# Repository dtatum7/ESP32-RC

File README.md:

ESP32 based remote control system with 8 PWM outputs reconfigurable as controller ADC inputs with SparkFun QWIIC / Adafruit STEMMA connections for easy customization.

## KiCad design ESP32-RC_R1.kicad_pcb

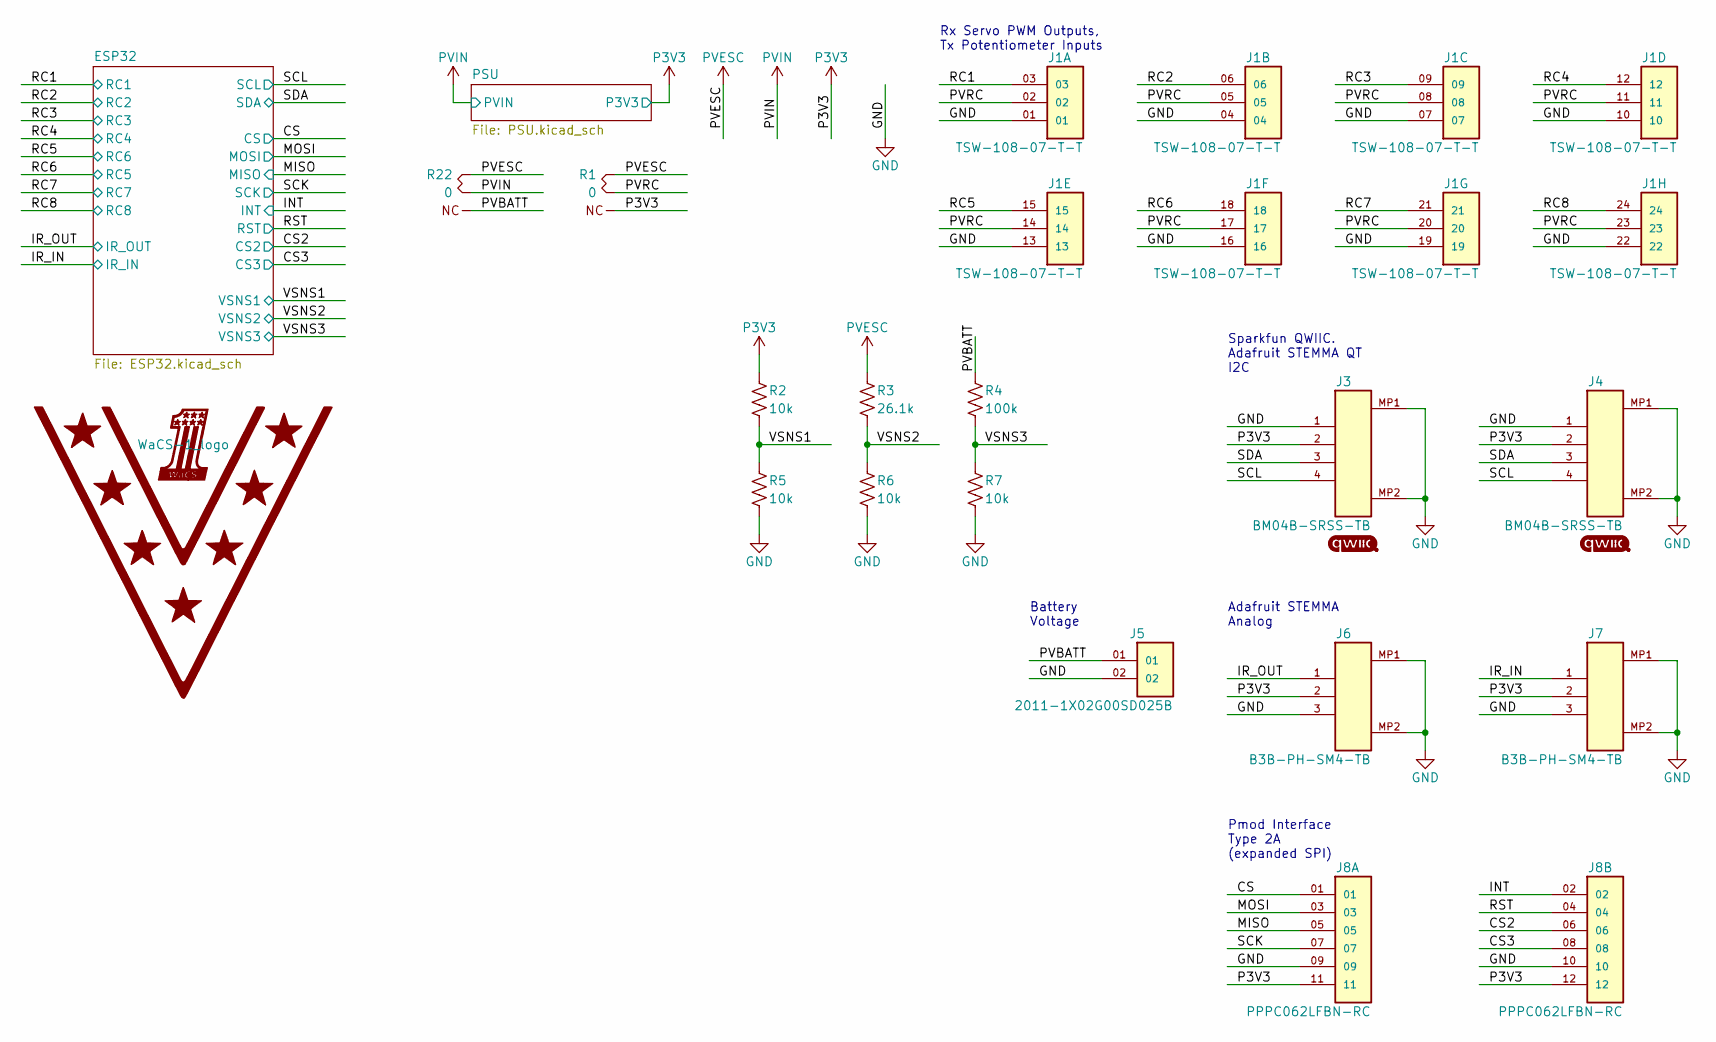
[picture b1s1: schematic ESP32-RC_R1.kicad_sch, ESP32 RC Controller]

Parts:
G1, G2: QWIIC_logo; MPN QWIIC_logo
G5: WaCS-1_logo; MPN WaCS-1_logo
G6: Champion logo; MPN Champion_Logo
J1: TSW-108-07-T-T; SAMTEC_TSW-108-07-T-T; MPN TSW-108-07-T-T
J3, J4: BM04B-SRSS-TB; BM04B-SRSS_JST; MPN BM04B-SRSS-TB
J5: 2011-1X02G00SD025B; MPN 2011-1X02G00SD025B
J6, J7: B3B-PH-SM4-TB; MPN B3B-PH-SM4-TB
J8: PPPC062LFBN-RC; MPN TSW-108-07-T-T
R1, R22: 0; R0603_3; MPN CRCW06030000Z0EAC
R2, R5, R6, R7: 10k; R0603; MPN CRCW060310K0FKEAC
R3: 26.1k; R0603; MPN CRCW060326K1FKEAC
R4: 100k; R0603; MPN CRCW0603100KFKEAC

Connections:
/CS: J8.01; also elsewhere on the board
/CS2: J8.06; also elsewhere on the board
/CS3: J8.08; also elsewhere on the board
/INT: J8.02; also elsewhere on the board
/IR_IN: J7.1; also elsewhere on the board
/IR_OUT: J6.1; also elsewhere on the board
/MISO: J8.05; also elsewhere on the board
/MOSI: J8.03; also elsewhere on the board
/PVBATT: J5.01, R4.1, R22.3
/PVRC: J1.02, J1.05, J1.08, J1.11, J1.14, J1.17, J1.20, J1.23, R1.2
/RC1: J1.03; also elsewhere on the board
/RC2: J1.06; also elsewhere on the board
/RC3: J1.09; also elsewhere on the board
/RC4: J1.12; also elsewhere on the board
/RC5: J1.15; also elsewhere on the board
/RC6: J1.18; also elsewhere on the board
/RC7: J1.21; also elsewhere on the board
/RC8: J1.24; also elsewhere on the board
/RST: J8.04; also elsewhere on the board
/SCK: J8.07; also elsewhere on the board
/SCL: J3.4, J4.4; also elsewhere on the board
/SDA: J3.3, J4.3; also elsewhere on the board
/VSNS1: R2.2, R5.1; also elsewhere on the board
/VSNS2: R3.2, R6.1; also elsewhere on the board
/VSNS3: R4.2, R7.1; also elsewhere on the board
GND: J1.01, J1.04, J1.07, J1.10, J1.13, J1.16, J1.19, J1.22, J3.1, J3.MP1, J3.MP2, J4.1, J4.MP1, J4.MP2, J5.02, J6.3, J6.MP1, J6.MP2, J7.3, J7.MP1, J7.MP2, J8.09, J8.10, R5.2, R6.2, R7.2; also elsewhere on the board
P3V3: J3.2, J4.2, J6.2, J7.2, J8.11, J8.12, R1.3, R2.1; also elsewhere on the board
PVESC: R1.1, R3.1, R22.1
PVIN: R22.2; also elsewhere on the board

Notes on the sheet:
Adafruit STEMMA Analog
Sparkfun QWIIC. Adafruit STEMMA QT I2C
Battery Voltage
Rx Servo PWM Outputs, Tx Potentiometer Inputs
Pmod Interface Type 2A (expanded SPI)

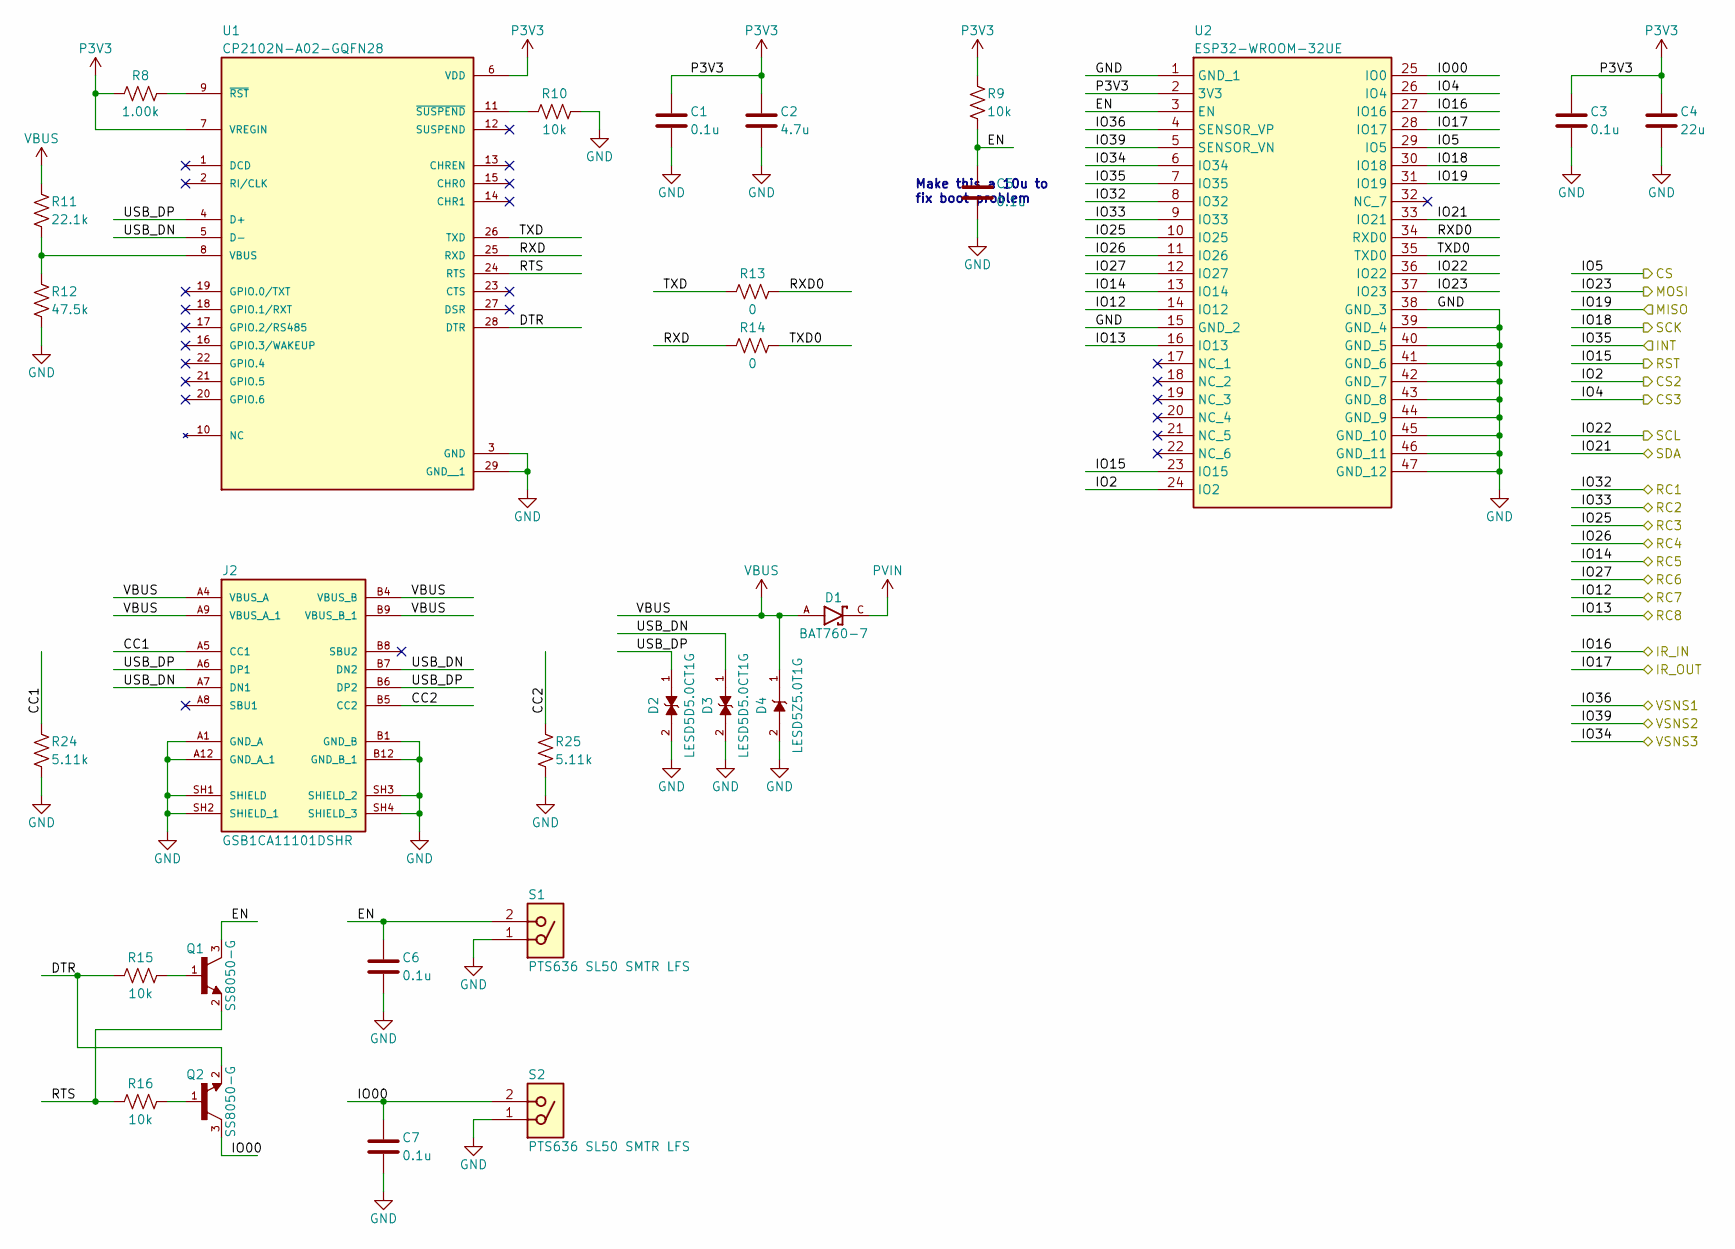
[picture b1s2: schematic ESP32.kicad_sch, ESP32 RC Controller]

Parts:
C1, C3, C5, C6, C7: 0.1u; C0603; MPN CC0603KRX7R7BB104
C2: 4.7u; C0603; MPN CL10A475KP8NNNC
C4: 22u; C0805; MPN CL21A226MOCLRNC
D1: BAT760-7; SOD-323; MPN BAT760-7
D2, D3: LESD5D5.0CT1G; SOD-523; MPN LESD5D5.0CT1G
D4: LESD5Z5.0T1G; SOD-523; MPN LESD5Z5.0T1G
J2: GSB1CA11101DSHR; AMPHENOL_GSB1CA11101DSHR; MPN GSB1CA11101DSHR
Q1, Q2: SS8050-G; SOT-23-3; MPN SS8050-G
R8: 1.00k; R0603; MPN CRCW06031K00FKEAC
R9, R10, R15, R16: 10k; R0603; MPN CRCW060310K0FKEAC
R11: 22.1k; R0603; MPN CRCW060322K1FKEAC
R12: 47.5k; R0603; MPN CRCW060347K5FKEAC
R13, R14: 0; R0603; MPN CRCW06030000Z0EAC
R24, R25: 5.11k; R0603; MPN CRCW06035K11FKEAC
S1, S2: PTS636 SL50 SMTR LFS; PTS636SL50SMTRLFS; MPN PTS636 SL50 SMTR LFS
U1: CP2102N-A02-GQFN28; 28-WFQFN; MPN CP2102N-A02-GQFN28
U2: ESP32-WROOM-32UE; ESP32-32UE_EXP; MPN ESP32-WROOM-32UE

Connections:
/CS: U2.29 (IO5); also elsewhere on the board
/CS2: U2.24 (IO2); also elsewhere on the board
/CS3: U2.26 (IO4); also elsewhere on the board
/ESP32/CC1: J2.A5 (CC1), R24.1
/ESP32/CC2: J2.B5 (CC2), R25.1
/ESP32/DTR: Q2.2, R15.1, U1.28 (DTR)
/ESP32/EN: C5.1, C6.1, Q1.3, R9.2, S1.2, U2.3 (EN)
/ESP32/IO00: C7.1, Q2.3, S2.2, U2.25 (IO0)
/ESP32/RTS: Q1.2, R16.1, U1.24 (RTS)
/ESP32/RXD: R14.1, U1.25 (RXD)
/ESP32/RXD0: R13.2, U2.34 (RXD0)
/ESP32/TXD: R13.1, U1.26 (TXD)
/ESP32/TXD0: R14.2, U2.35 (TXD0)
/ESP32/USB_DN: D3.1, J2.A7 (DN1), J2.B7 (DN2), U1.5 (D-)
/ESP32/USB_DP: D2.1, J2.A6 (DP1), J2.B6 (DP2), U1.4 (D+)
/INT: U2.7 (IO35); also elsewhere on the board
/IR_IN: U2.27 (IO16); also elsewhere on the board
/IR_OUT: U2.28 (IO17); also elsewhere on the board
/MISO: U2.31 (IO19); also elsewhere on the board
/MOSI: U2.37 (IO23); also elsewhere on the board
/RC1: U2.8 (IO32); also elsewhere on the board
/RC2: U2.9 (IO33); also elsewhere on the board
/RC3: U2.10 (IO25); also elsewhere on the board
/RC4: U2.11 (IO26); also elsewhere on the board
/RC5: U2.12 (IO27); also elsewhere on the board
/RC6: U2.13 (IO14); also elsewhere on the board
/RC7: U2.14 (IO12); also elsewhere on the board
/RC8: U2.16 (IO13); also elsewhere on the board
/RST: U2.23 (IO15); also elsewhere on the board
/SCK: U2.30 (IO18); also elsewhere on the board
/SCL: U2.36 (IO22); also elsewhere on the board
/SDA: U2.33 (IO21); also elsewhere on the board
/VSNS1: U2.4 (SENSOR_VP); also elsewhere on the board
/VSNS2: U2.5 (SENSOR_VN); also elsewhere on the board
/VSNS3: U2.6 (IO34); also elsewhere on the board
GND: C1.2, C2.2, C3.2, C4.2, C5.2, C6.2, C7.2, D2.2, D3.2, D4.2, J2.A1 (GND_A), J2.A12 (GND_A_1), J2.B1 (GND_B), J2.B12 (GND_B_1), J2.SH1 (SHIELD), J2.SH2 (SHIELD_1), J2.SH3 (SHIELD_2), J2.SH4 (SHIELD_3), R10.2, R12.2, R24.2, R25.2, S1.1, S2.1, U1.3 (GND), U1.29 (GND__1), U2.1 (GND_1), U2.15 (GND_2), U2.38 (GND_3), U2.39 (GND_4), U2.40 (GND_5), U2.41 (GND_6), U2.42 (GND_7), U2.43 (GND_8), U2.44 (GND_9), U2.45 (GND_10), U2.46 (GND_11), U2.47 (GND_12); also elsewhere on the board
unnamed: Q1.1, R15.2
unnamed: Q2.1, R16.2
unnamed: R11.2, R12.1, U1.8 (VBUS)
unnamed: R8.2, U1.9 (~RST)
unnamed: R10.1, U1.11 (~SUSPEND)
P3V3: C1.1, C2.1, C3.1, C4.1, R8.1, R9.1, U1.6 (VDD), U1.7 (VREGIN), U2.2 (3V3); also elsewhere on the board
PVIN: D1.C; also elsewhere on the board
VBUS: D1.A, D4.1, J2.A4 (VBUS_A), J2.A9 (VBUS_A_1), J2.B4 (VBUS_B), J2.B9 (VBUS_B_1), R11.1

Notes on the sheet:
Make this a 10u to fix boot problem

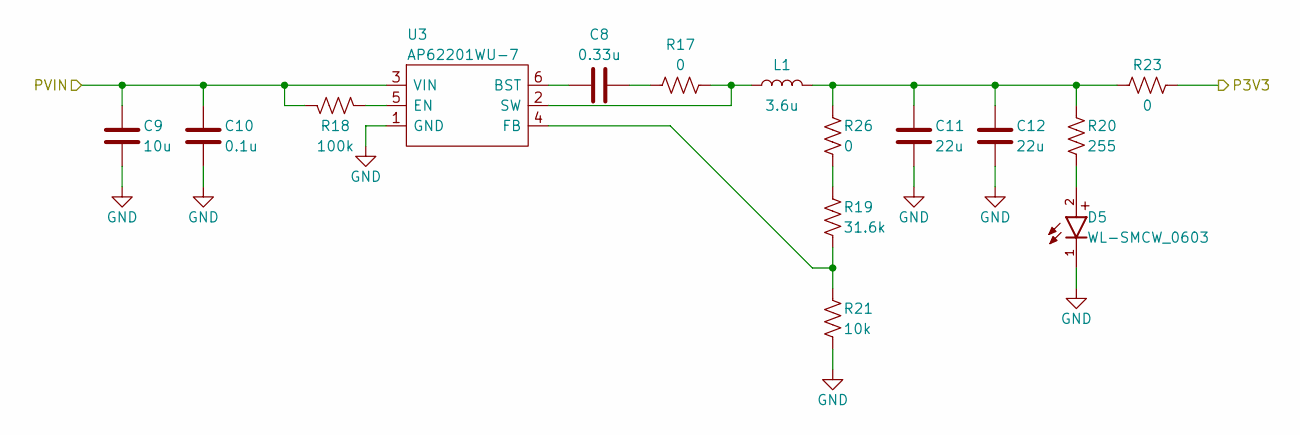
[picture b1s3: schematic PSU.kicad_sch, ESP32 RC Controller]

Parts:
C8: 0.33u; C0603; MPN CL10B334KO8NNNC
C9: 10u; C0805; MPN CL21A106KOQNNNE
C10: 0.1u; C0603; MPN CC0603KRX7R7BB104
C11, C12: 22u; C0805; MPN CL21A226MOCLRNC
D5: WL-SMCW_0603; MPN 150060VS75000
L1: 3.6u; L3131; MPN LSXNH8080YBL3R3NJG
R17, R23, R26: 0; R0603; MPN CRCW06030000Z0EAC
R18: 100k; R0603; MPN CRCW0603100KFKEAC
R19: 31.6k; R0603; MPN CRCW060331K6FKEAC
R20: 255; R0603; MPN CRCW0603255RFKEAC
R21: 10k; R0603; MPN CRCW060310K0FKEAC
U3: AP62201WU-7; TSOT26; MPN AP62201WU-7

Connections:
GND: C9.2, C10.2, C11.2, C12.2, D5.1, R21.2, U3.1 (GND); also elsewhere on the board
unnamed: C8.2, R17.1
unnamed: C11.1, C12.1, L1.2, R20.1, R23.1, R26.1
unnamed: D5.2, R20.2
unnamed: R19.1, R26.2
unnamed: C8.1, U3.6 (BST)
unnamed: R18.2, U3.5 (EN)
unnamed: R19.2, R21.1, U3.4 (FB)
unnamed: L1.1, R17.2, U3.2 (SW)
P3V3: R23.2; also elsewhere on the board
PVIN: C9.1, C10.1, R18.1, U3.3 (VIN); also elsewhere on the board

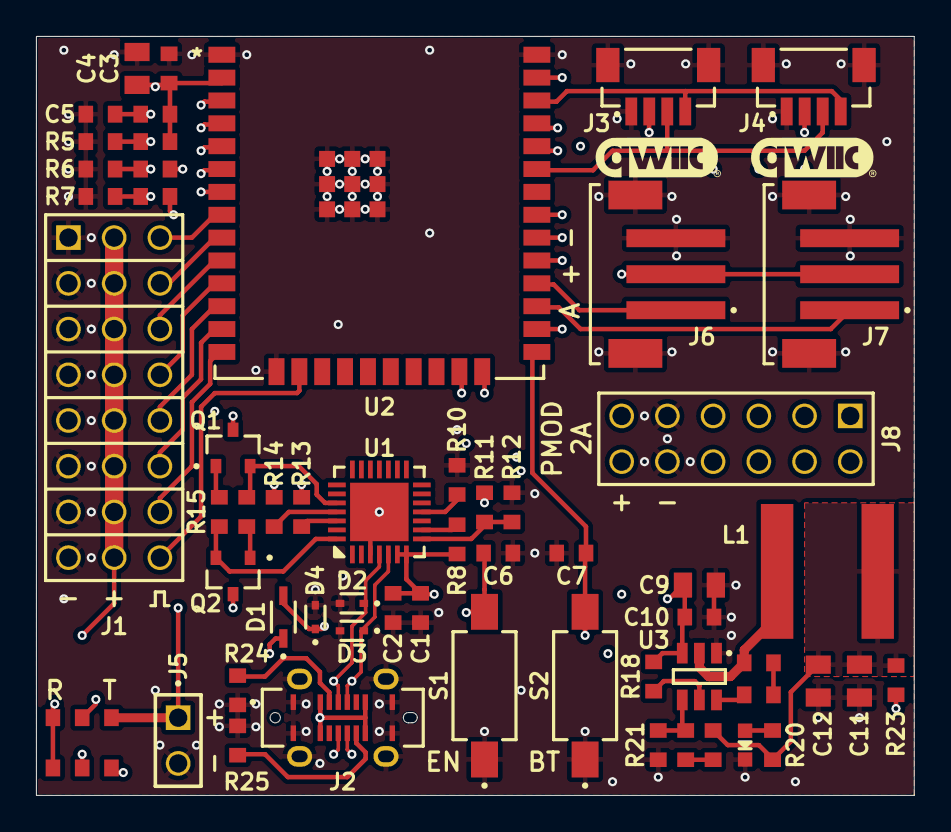
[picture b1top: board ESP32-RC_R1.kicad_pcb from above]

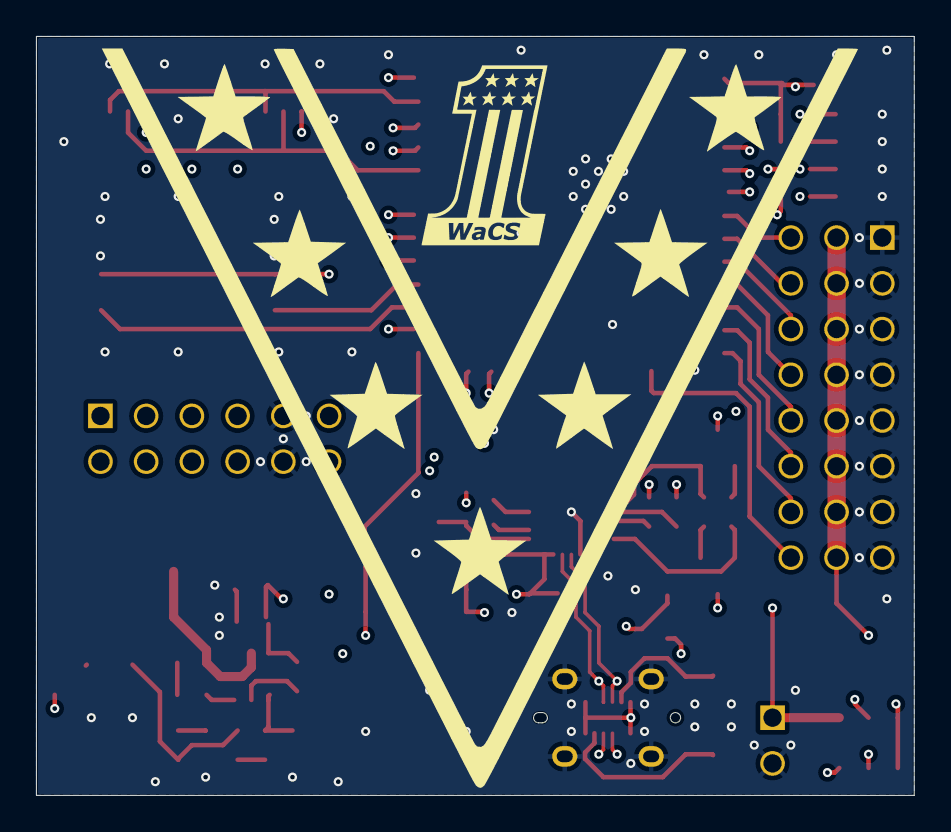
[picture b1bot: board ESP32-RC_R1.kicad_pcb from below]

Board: 4 copper layers, 48.8 x 42.2 mm, 63 parts (2 on the bottom side), 55 nets.

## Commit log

2024-09-05 Add files via upload
    Initial commit of ESP32 RC project. Library needs a good bit of cleanup.
2024-09-10 Description
2025-03-25 R1
    ESP32-R1
